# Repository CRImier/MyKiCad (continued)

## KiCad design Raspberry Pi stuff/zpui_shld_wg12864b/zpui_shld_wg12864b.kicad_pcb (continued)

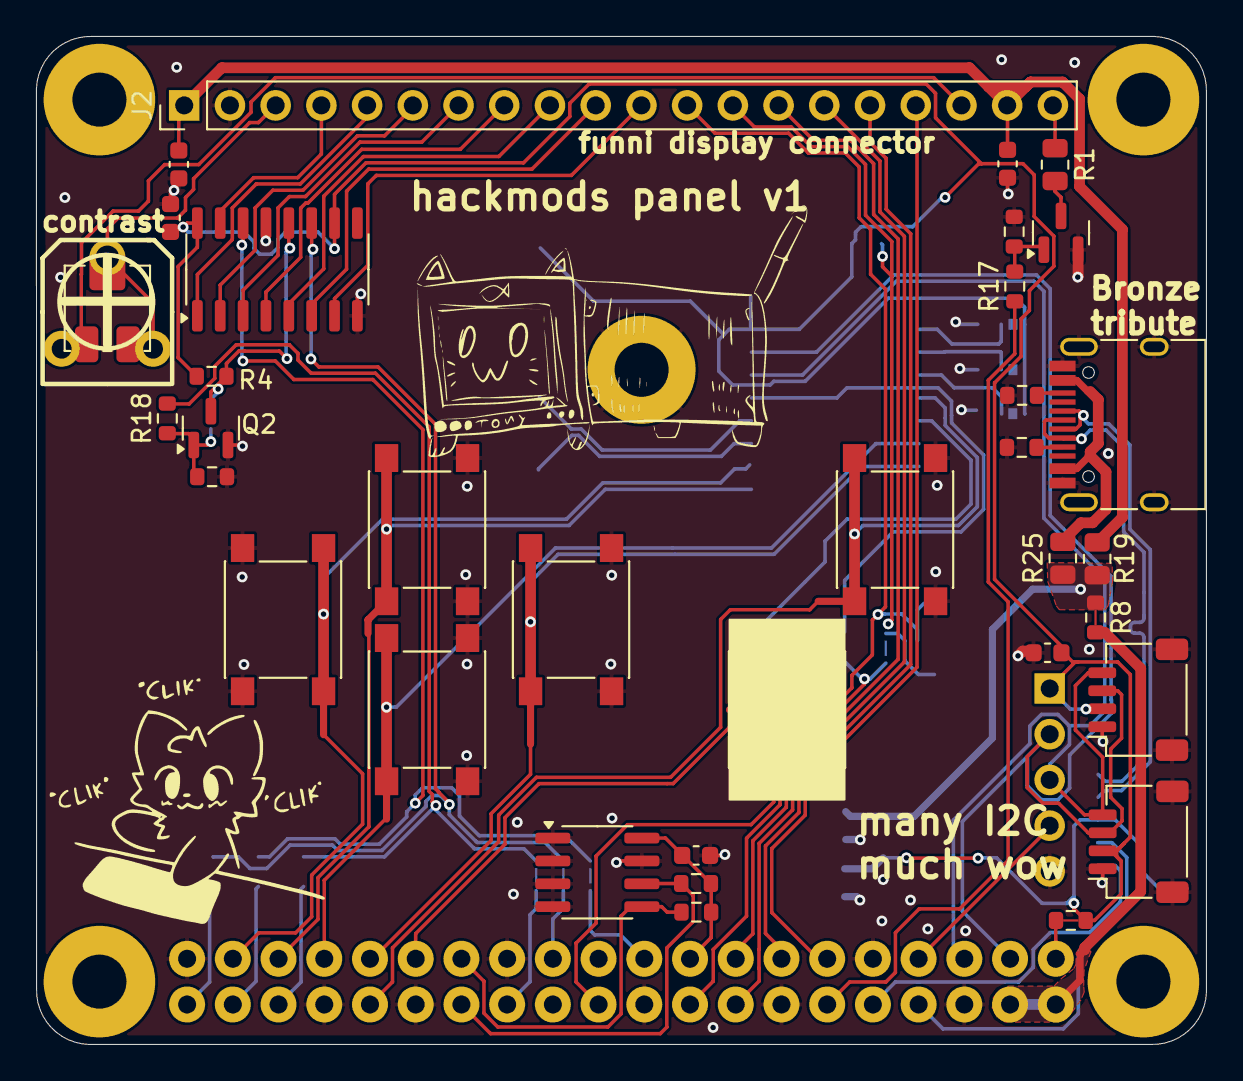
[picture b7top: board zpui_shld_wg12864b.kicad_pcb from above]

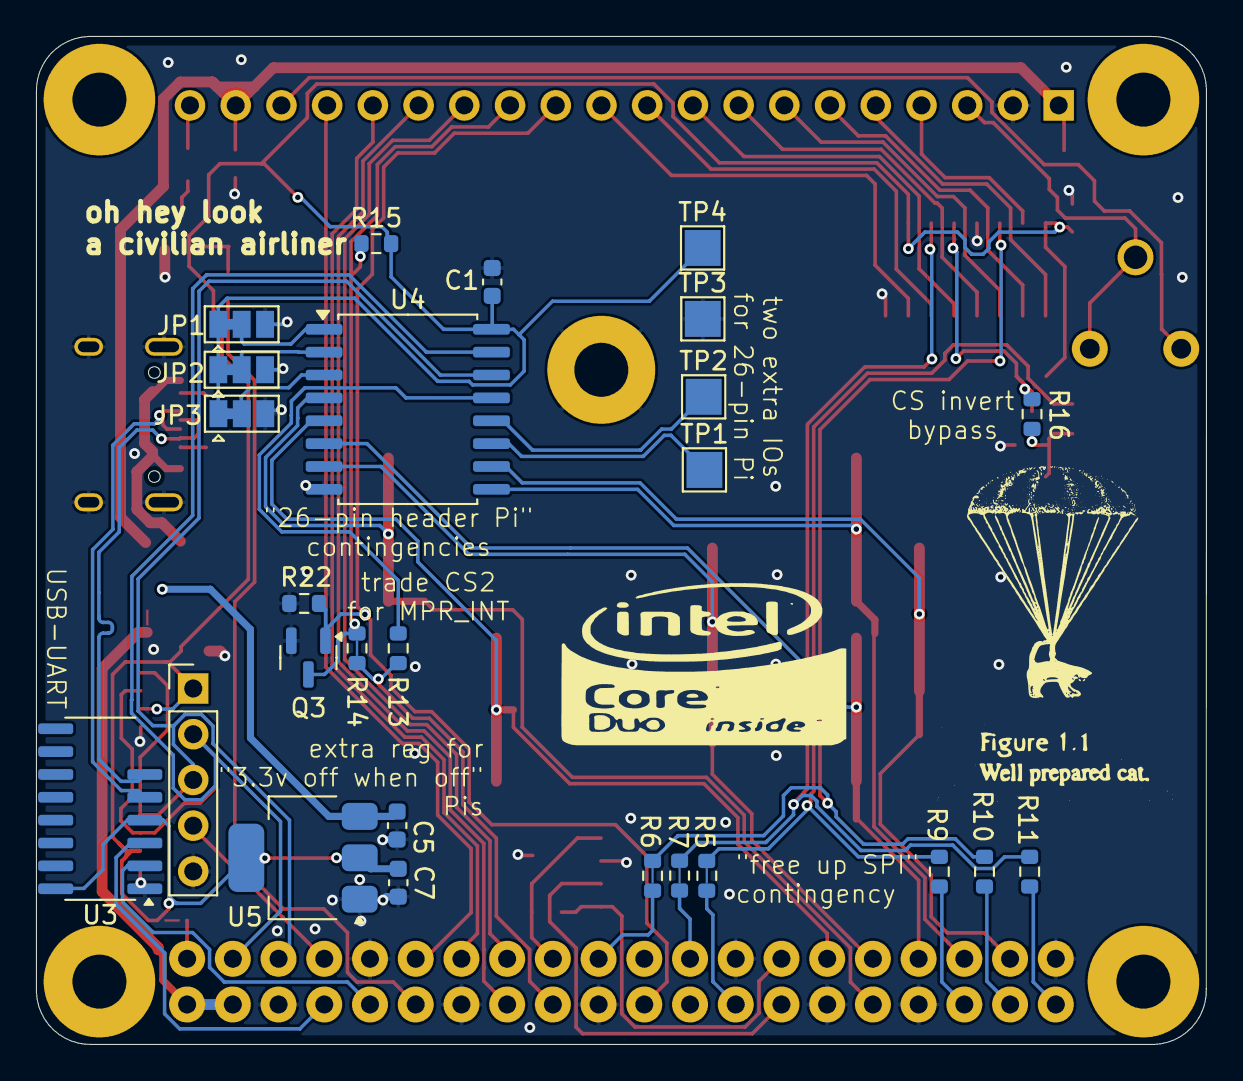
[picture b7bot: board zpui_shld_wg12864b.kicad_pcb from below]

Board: 2 copper layers, 65.0 x 56.0 mm, 63 parts (26 on the bottom side), 63 nets.

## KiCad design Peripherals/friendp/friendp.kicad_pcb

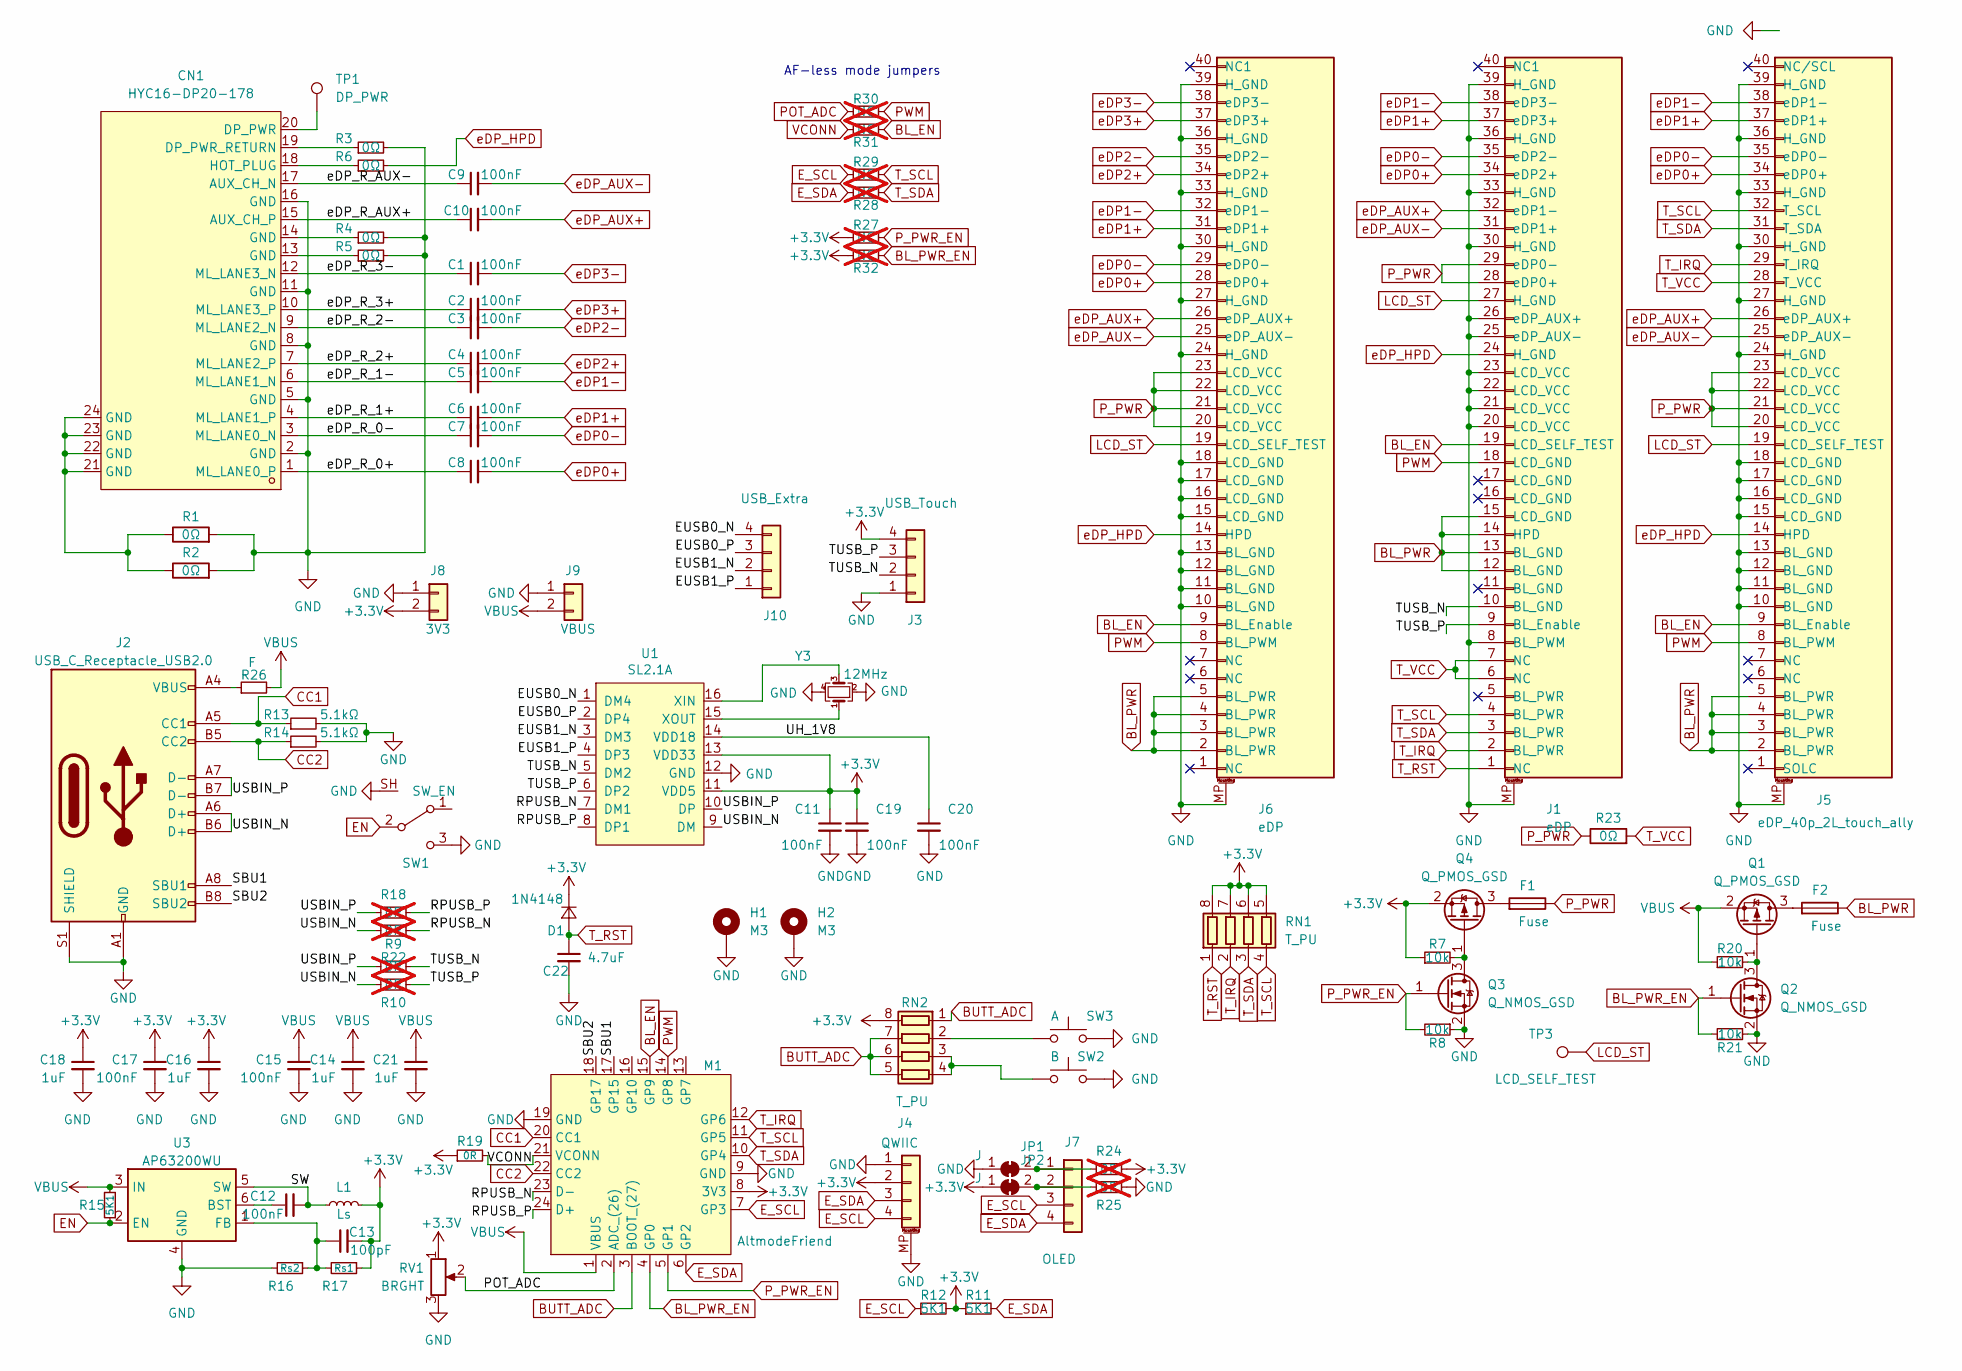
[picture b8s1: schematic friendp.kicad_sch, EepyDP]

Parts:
C1, C2, C3, C4, C5, C6, C7, C8, C9, C10: 100nF; C_0402_1005Metric
C11, C12, C17, C19, C20: 100nF; C_0603_1608Metric
C13: 100pF; C_0603_1608Metric
C14, C16, C18, C21: 1uF; C_0805_2012Metric
C15: 100nF; C_0805_2012Metric
C22: 4.7uF; C_0805_2012Metric
CN1: HYC16-DP20-178; DP-SMD_HYC16-DP20-178; LCSC Part C711350
D1: 1N4148; D_SOD-123F
F1, F2: Fuse; Fuse_0805_2012Metric
H1, H2: M3; MountingHole_3.2mm_M3_Pad
J1, J6: eDP; TE_4-1734839-0_1x40-1MP_P0.5mm_Horizontal
J2: USB_C_Receptacle_USB2.0; USB_C_Receptacle_HRO_TYPE-C-31-M-12
J3: USB_Touch; PinHeader_1x04_P2.54mm_Vertical
J4: QWIIC; JST_SH_SM04B-SRSS-TB_1x04-1MP_P1.00mm_Horizontal
J5: eDP_40p_2L_touch_ally; TE_4-1734839-0_1x40-1MP_P0.5mm_Horizontal
J7: OLED; PinHeader_1x04_P2.54mm_Vertical
J8: 3V3; PinHeader_1x02_P2.54mm_Vertical
J9: VBUS; PinHeader_1x02_P2.54mm_Vertical
J10: USB_Extra; PinHeader_1x04_P2.54mm_Vertical
JP1, JP2: J; R_0603_1608Metric_Jumper
L1: Ls; L_Bourns-SRN4018
M1: AltmodeFriend; altmode_friend
Q1, Q4: Q_PMOS_GSD; SOT-23
Q2, Q3: Q_NMOS_GSD; SOT-23
R1, R2: 0Ω; R_0603_1608Metric
R3, R4, R5, R6, R23: 0Ω; R_0603_1608Metric_Jumper
R7, R8, R20, R21: 10k; R_0603_1608Metric
R9, R10, R18, R22, R24, R25: 0R; R_0603_1608Metric; not fitted
R11, R12, R15: 5K1; R_0603_1608Metric
R13, R14: 5.1kΩ; R_0603_1608Metric
R16: Rs2; R_0603_1608Metric
R17: Rs1; R_0603_1608Metric
R19: 0R; R_0603_1608Metric_Jumper
R26: F; R_0805_2012Metric
R27, R28, R29, R30, R31, R32: NC; R_0603_1608Metric; not fitted
RN1, RN2: T_PU; R_Array_Convex_4x0603
RV1: BRGHT; RES-ADJ-TH_VZ067TL1B202
SW1: SW_EN; SW_SPDT_PCM12_SH
SW2: B; SW_SPST_FSMSM
SW3: A; SW_SPST_FSMSM
TP1: DP_PWR; TestPoint_Pad_1.0x1.0mm
TP3: LCD_SELF_TEST; TestPoint_Pad_1.0x1.0mm
U1: SL2.1A; SO-16_3.9x9.9mm_P1.27mm
U3: AP63200WU; TSOT-23-6
Y3: 12MHz; Crystal_SMD_3225-4Pin_3.2x2.5mm

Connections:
+3.3V: C11.1, C13.2, C16.1, C17.1, C18.1, C19.1, D1.1 (K), J3.4, J4.2, J8.2, JP2.1 (A), L1.2, M1.8 (3V3), Q4.2 (S), R7.1, R11.1, R12.2, R17.1, R19.1, R24.1, R27.1, R32.1, RN1.5 (R4.2), RN1.6 (R3.2), RN1.7 (R2.2), RN1.8 (R1.2), RN2.8 (R1.2), RV1.1, U1.11 (VDD5), U1.13 (VDD33)
/EUSB0_N: J10.4, U1.1 (DM4)
/EUSB0_P: J10.3, U1.2 (DP4)
/EUSB1_N: J10.2, U1.3 (DM3)
/EUSB1_P: J10.1, U1.4 (DP3)
/RPUSB_N: M1.23 (D-), R22.1, U1.7 (DM1)
/RPUSB_P: M1.24 (D+), R18.1, U1.8 (DP1)
/SBU1: J2.A8 (SBU1), M1.17 (GP15)
/SBU2: J2.B8 (SBU2), M1.18 (GP17)
/SW: C12.2, L1.1, U3.5 (SW)
/TUSB_N: J1.10 (BL_GND), J3.2, R9.1, U1.5 (DM2)
/TUSB_P: J1.9 (BL_Enable), J3.3, R10.1, U1.6 (DP2)
/UH_1V8: C20.1, U1.14 (VDD18)
/USBIN_N: J2.A6 (D+), J2.B6 (D+), R10.2, R22.2, U1.9 (DM)
/USBIN_P: J2.A7 (D-), J2.B7 (D-), R9.2, R18.2, U1.10 (DP)
/eDP_R_0+: C8.1, CN1.1 (ML_LANE0_P)
/eDP_R_0-: C7.1, CN1.3 (ML_LANE0_N)
/eDP_R_1+: C6.1, CN1.4 (ML_LANE1_P)
/eDP_R_1-: C5.1, CN1.6 (ML_LANE1_N)
/eDP_R_2+: C4.1, CN1.7 (ML_LANE2_P)
/eDP_R_2-: C3.1, CN1.9 (ML_LANE2_N)
/eDP_R_3+: C2.1, CN1.10 (ML_LANE3_P)
/eDP_R_3-: C1.1, CN1.12 (ML_LANE3_N)
/eDP_R_AUX+: C10.1, CN1.15 (AUX_CH_P)
/eDP_R_AUX-: C9.1, CN1.17 (AUX_CH_N)
BL_EN: J1.19 (LCD_SELF_TEST), J5.9 (BL_Enable), J6.9 (BL_Enable), M1.15 (GP9), R31.2
BL_PWR: F2.1, J1.12 (BL_GND), J1.13 (BL_GND), J1.14 (HPD), J1.15 (LCD_GND), J5.2 (BL_PWR), J5.3 (BL_PWR), J5.4 (BL_PWR), J5.5 (BL_PWR), J6.2 (BL_PWR), J6.3 (BL_PWR), J6.4 (BL_PWR), J6.5 (BL_PWR)
BL_PWR_EN: M1.4 (GP0), Q2.1 (G), R21.2, R32.2
BUTT_ADC: M1.3 (BOOT_(27)), RN2.1 (R1.1), RN2.5 (R4.2), RN2.6 (R3.2), RN2.7 (R2.2)
CC1: J2.A5 (CC1), M1.20 (CC1), R13.1
CC2: J2.B5 (CC2), M1.22 (CC2), R14.1
EN: R15.1, SW1.2 (B), U3.2 (EN)
E_SCL: J4.4, J7.3, M1.7 (GP3), R12.1, R29.1
E_SDA: J4.3, J7.4, M1.6 (GP2), R11.2, R28.1
GND: C11.2, C14.2, C15.2, C16.2, C17.2, C18.2, C19.2, C20.2, C21.2, C22.2, CN1.2 (GND), CN1.5 (GND), CN1.8 (GND), CN1.11 (GND), CN1.16 (GND), H1.1, H2.1, J1.8 (BL_PWM), J1.20 (LCD_VCC), J1.21 (LCD_VCC), J1.22 (LCD_VCC), J1.23 (LCD_VCC), J1.25 (eDP_AUX-), J1.26 (eDP_AUX+), J1.30 (H_GND), J1.33 (H_GND), J1.36 (H_GND), J1.39 (H_GND), J1.MP, J2.A1 (GND), J2.A12 (GND), J2.B1 (GND), J2.B12 (GND), J2.S1 (SHIELD), J3.1, J4.1, J4.MP (MountPin), J5.10 (BL_GND), J5.11 (BL_GND), J5.12 (BL_GND), J5.13 (BL_GND), J5.15 (LCD_GND), J5.16 (LCD_GND), J5.17 (LCD_GND), J5.18 (LCD_GND), J5.24 (H_GND), J5.27 (H_GND), J5.30 (H_GND), J5.33 (H_GND), J5.36 (H_GND), J5.39 (H_GND), J5.MP, J6.10 (BL_GND), J6.11 (BL_GND), J6.12 (BL_GND), J6.13 (BL_GND), J6.15 (LCD_GND), J6.16 (LCD_GND), J6.17 (LCD_GND), J6.18 (LCD_GND), J6.24 (H_GND), J6.27 (H_GND), J6.30 (H_GND), J6.33 (H_GND), J6.36 (H_GND), J6.39 (H_GND), J6.MP, J8.1, J9.1, JP1.1 (A), M1.9 (GND), M1.19 (GND), Q2.2 (S), Q3.2 (S), R1.2, R2.2, R3.2, R4.2, R5.2, R8.1, R13.2, R14.2, R16.2, R21.1, R25.1, RV1.3, SW1.3 (C), SW1.SH, SW2.1, SW3.1, U1.12 (GND), U3.4 (GND), Y3.2, Y3.4
LCD_ST: J1.27 (H_GND), J5.19 (LCD_SELF_TEST), J6.19 (LCD_SELF_TEST), TP3.1
unnamed: CN1.20 (DP_PWR), TP1.1
unnamed: CN1.19 (DP_PWR_RETURN), R3.1
unnamed: CN1.13 (GND), R5.1
unnamed: CN1.14 (GND), R4.1
unnamed: CN1.21 (GND), CN1.22 (GND), CN1.23 (GND), CN1.24 (GND), R1.1, R2.1
unnamed: CN1.18 (HOT_PLUG), R6.1
unnamed: J2.A4 (VBUS), J2.A9 (VBUS), J2.B4 (VBUS), J2.B9 (VBUS), R26.1
unnamed: J7.1, JP1.2 (B), R24.2
unnamed: J7.2, JP2.2 (B), R25.2
unnamed: F2.2, Q1.3 (D)
unnamed: Q1.1 (G), Q2.3 (D), R20.2
unnamed: Q3.3 (D), Q4.1 (G), R7.2
unnamed: F1.2, Q4.3 (D)
unnamed: RN2.2 (R2.1), SW3.2
unnamed: RN2.3 (R3.1), RN2.4 (R4.1), SW2.2
unnamed: U1.16 (XIN), Y3.3
unnamed: U1.15 (XOUT), Y3.1
unnamed: C12.1, U3.6 (BST)
unnamed: C13.1, R16.1, R17.2, U3.1 (FB)
POT_ADC: M1.2 (ADC_(26)), R30.1, RV1.2
PWM: J1.18 (LCD_GND), J5.8 (BL_PWM), J6.8 (BL_PWM), M1.14 (GP8), R30.2
P_PWR: F1.1, J1.28 (eDP0+), J1.29 (eDP0-), J5.20 (LCD_VCC), J5.21 (LCD_VCC), J5.22 (LCD_VCC), J5.23 (LCD_VCC), J6.20 (LCD_VCC), J6.21 (LCD_VCC), J6.22 (LCD_VCC), J6.23 (LCD_VCC), R23.1
P_PWR_EN: M1.5 (GP1), Q3.1 (G), R8.2, R27.2
T_IRQ: J1.2 (BL_PWR), J5.29 (T_IRQ), M1.12 (GP6), RN1.2 (R2.1)
T_RST: C22.1, D1.2 (A), J1.1 (NC), RN1.1 (R1.1)
T_SCL: J1.4 (BL_PWR), J5.32 (T_SCL), M1.11 (GP5), R29.2, RN1.4 (R4.1)
T_SDA: J1.3 (BL_PWR), J5.31 (T_SDA), M1.10 (GP4), R28.2, RN1.3 (R3.1)
T_VCC: J1.6 (NC), J1.7 (NC), J5.28 (T_VCC), R23.2
VBUS: C14.1, C15.1, C21.1, J9.2, M1.1 (VBUS), Q1.2 (S), R15.2, R20.1, R26.2, U3.3 (IN)
VCONN: M1.21 (VCONN), R19.2, R31.1
eDP0+: C8.2, J1.34 (eDP2+), J5.34 (eDP0+), J6.28 (eDP0+)
eDP0-: C7.2, J1.35 (eDP2-), J5.35 (eDP0-), J6.29 (eDP0-)
eDP1+: C6.2, J1.37 (eDP3+), J5.37 (eDP1+), J6.31 (eDP1+)
eDP1-: C5.2, J1.38 (eDP3-), J5.38 (eDP1-), J6.32 (eDP1-)
eDP2+: C4.2, J6.34 (eDP2+)
eDP2-: C3.2, J6.35 (eDP2-)
eDP3+: C2.2, J6.37 (eDP3+)
eDP3-: C1.2, J6.38 (eDP3-)
eDP_AUX+: C10.2, J1.32 (eDP1-), J5.26 (eDP_AUX+), J6.26 (eDP_AUX+)
eDP_AUX-: C9.2, J1.31 (eDP1+), J5.25 (eDP_AUX-), J6.25 (eDP_AUX-)
eDP_HPD: J1.24 (H_GND), J5.14 (HPD), J6.14 (HPD), R6.2

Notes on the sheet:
AF-less mode jumpers

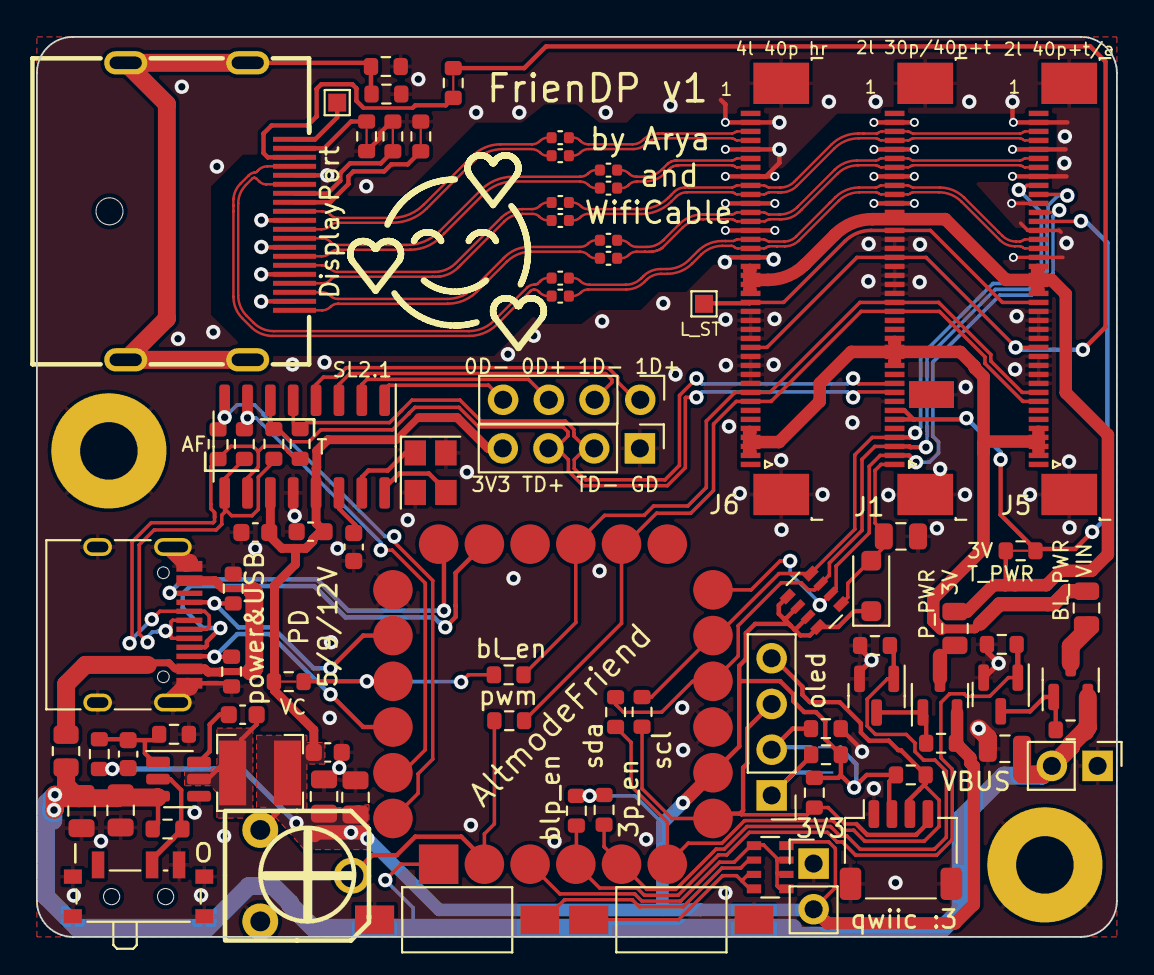
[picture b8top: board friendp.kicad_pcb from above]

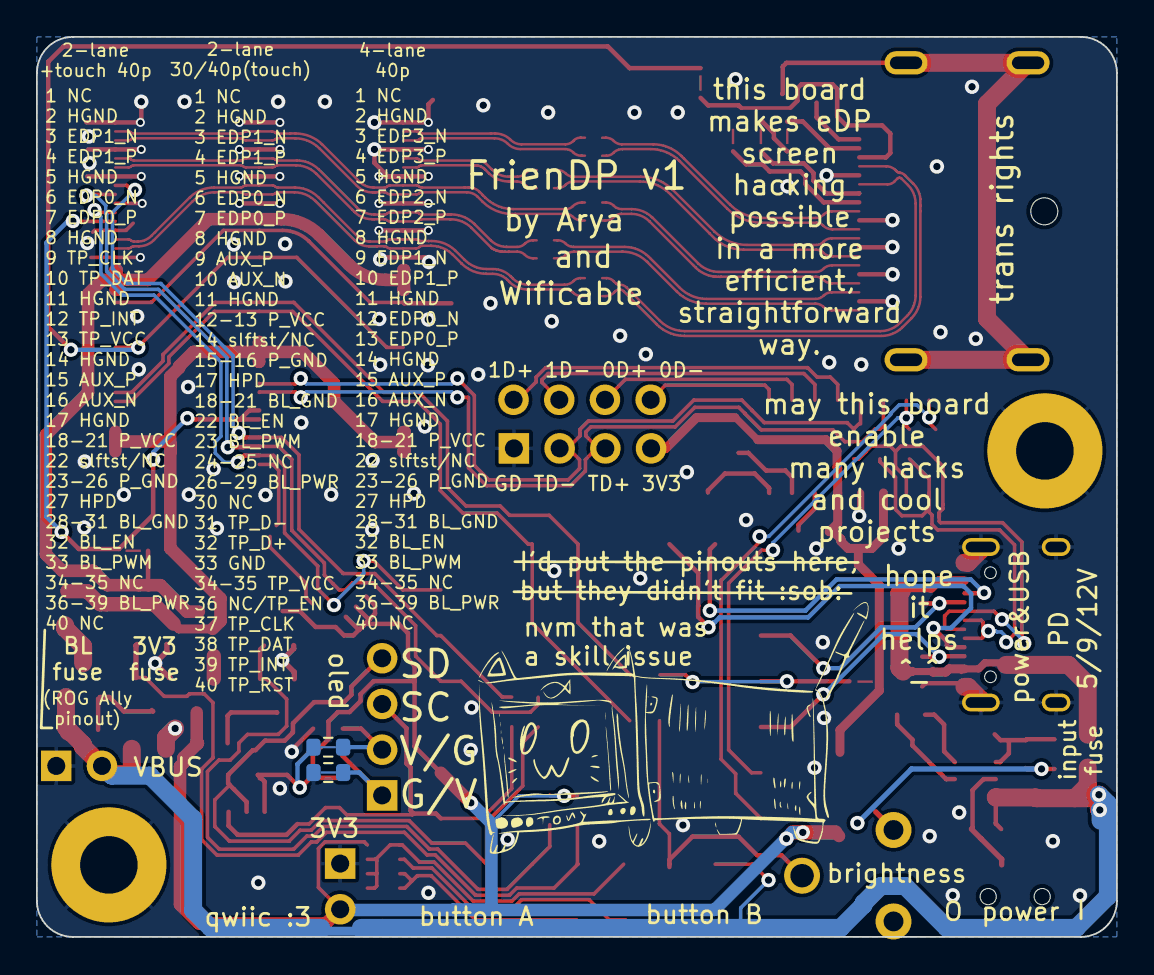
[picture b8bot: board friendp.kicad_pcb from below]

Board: 4 copper layers, 60.0 x 50.0 mm, 89 parts (2 on the bottom side), 77 nets.

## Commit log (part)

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2019-07-22 Feeling lucky, might push -f later
2019-10-12 Adding fp-info-cache to .gitignore
2019-10-12 Adding "rescue" files to gitignore
2019-10-12 Adding SaferSpace files
2019-11-12 Adding SY6280 breakout - v1 finished
2019-11-12 Adding the 74HC125-1G breakout (need to check footprint)
2019-11-12 Adding the 74HC245 DIP breakout - v1, should work
2019-11-15 595 SMD breakout changes (forgot what exactly)
2019-11-15 PCF8574 breakout WIP
2019-11-15 SY6280 breakout changes (forgot what exactly)
2019-11-15 74HC245 breakout changes (forgot what exactly)
2019-11-15 Pi PWM breakout changes (forgot what exactly)
2019-11-15 PCF8574 breakout - directory was not created correctly, moving
2019-11-15 PCF8574 breakout: did not close KiCad before commit, fixing
2019-11-18 Blank files for Ericsson PKF4000 breakout
2019-11-18 Adding PKF4000 datasheet
2019-11-19 Generating gerbers, adding some silk to the PCF8574 board
2019-11-19 Adding the 4x NPN breakout PCB
2019-11-19 Adding the S29ALxxxD breakout
2020-03-04 Adding power lane 90 degree arc PCBs for 2 and 3 lanes, 2 and 4 cm radius
2020-03-04 Removing fp-info-cache file
2020-03-04 Adding SIM net labels to mPCI-E breakout - SIM slot not fixed yet
2020-03-04 Improving MakeRiga keychain PCBs
2020-03-04 Minor PCF8574 breakout changes
2020-03-04 Adding MicroUSB breakouts - with and without a 3.3V regulator spot
2020-03-04 Adding files for a small power bus with a cap
2020-03-04 Parallel EEPROM reader files - not tested or anything, do not rely on it
2020-03-04 Gitignore-ing a bunch of stuff
2020-03-04 Adding self-playing piano solenoid controller PCB - P transistor footprint has wrong pinout and one of the 2-pin power connector footprints has reverse polarity, needs to be fixed.
2020-03-09 Adding a README for the Keyboard Whiz
2020-03-28 Adding Lenovo Flex 2-14 reverse-engineering top assembly FPC reverse-engineering effort
2020-08-26 Fixing confusion with Lenovo Flex 2 14 reverse-engineering files
2020-10-15 Adding JST-SH 4-pin and 6-pin breakouts
2020-10-15 Adding MAX14689 breakout files
2020-10-15 Adding a README to the microusb_breakout_with_reg board, with a small bug disclaimer.
2020-10-15 Fixing the microusb_breakout_with_reg board bug and removing the README disclaimer
2020-10-15 Adding the laptop_smartcard_socket_fpc_breakout board
2020-10-15 Adding *.sch-bak files to gitignore
2020-10-15 Changing the 48V relay breakout board so that all the SMD components are mounted on the bottom side => easier to assemble
2020-11-06 Adding the Raspberry Pi 400 GPIO adapter files - v1
2020-11-08 Adding README, pictures and proper 3d models to the Pi 400 GPIO adapter board
2021-01-05 Pi 400 GPIO breakout v2. Adding this in part because I'll try to re-route it now and might fail at that, so will need to fall back to the previous version.
    Force pushed later on - forgot to regenerate zones.
2021-01-05 Updated version of the fan_pwm_disconnecter board, this is what I'll be ordering
2021-01-15 Adding x2 panel files for mPCIe breakout board
2021-01-15 Adding TTP229BSF breakout board files with README
2021-01-15 Adding fan_pwm_disconnecter panel files
2021-01-15 Gitignore-ing panel gerber folders
2021-01-15 Adding a template line for "this repo also contains panel files"
2021-09-26 Updating and renaming a 48V relay breakout PCB, sch is broken and no idea how to fix it, really - maybe eventually. Also adding a 2x9 panel that fits inside JLCPCB 10x10 dimensions, though will take 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
2021-09-26 Adding a README and changing the on-PCB text to say "v2" because that's what it is. Need to also update the panel text sometime soon.
2021-09-26 Video I2C helper v1 added
2021-10-01 Added an 0R resistor in series with VCC on the simple NPN driver
2021-10-04 Adding the ATTIny universal fan controller board - unchecked for now, will be going over it later
2021-10-04 gitignore-ing the .pdf and .svg files again, also adding panel gerber folders to gitignore
2021-10-05 Adding Display Debuggaloo board v1
2021-10-05 Adding yet another MakeRiga keychain
2021-10-12 Adding the Pinecil 24V enjoyer board
2021-10-13 Adding the 0.69 display breakout
2021-10-15 Changed the HDMI plug in the Video I2C helper to correct pin numbering, rerouted traces to match, added shield connection to the SPDT switch symbol and pinout
2021-10-15 This is GPLv3, always has been
2021-10-15 Adding a "recommended thickness" line, adding it to READMEs where it fits
2021-10-15 Adding the uSD FPC breakout board
2021-10-17 Adding the K1-1210UN-01 switch breakout, with symbol and footprint
2021-10-18 Moving the MicroUSB socket to the top layer so that the board is easier to assemble, rearranging silkscreen a bit
2021-10-20 Adding the small MAX3232 breakout
2021-10-20 Adding a B+M to M-key 2230-2242 adapter
2021-10-20 Removing a bit of unneeded text
2021-10-27 Adding the reversed mPCIe to NVMe adapter. A non-reversed version coming soon!
2021-10-27 Adding more documentation to the NVMe BM to M card README
2021-11-03 Adding the mPCIe-NVMe board (non-reversed)
2021-11-03 Rerouted diffpairs to NVMe BM to M adapter, made the adapter longer, added holes so that part of the adapter can be snipped off for length decrease
2021-11-05 Adding the USB-B-to-MicroUSB board files, from https://gitlab.com/salfter/arduino-micro-usb-mod, then modified by me
2021-11-05 Adding the USB-A to Type-C converter board
2021-11-05 Adding the Neopixel to RS485 board
2021-11-05 Adding the single-sided version of the Neopixel to RS485 board
2021-11-07 Adding an ADJ resistor to the 1117-15 on the backside, rerouting diffpairs to decrease impedance a little bit
2021-11-07 Gerber export setting fixes - mostly changing "(excludeedgelayer false)" to "true)"
2021-11-09 Enabling more layers for export in the Tizen uSD breakout
2021-11-09 Fixing a README typo
2021-11-10 Adding a Type-C receptacle with holes-for-slots - just in case it's ever needed ig?
2021-11-10 Adding an M.2 AE to M-key adapter
2021-11-16 Adding a README to the repo itself, also adding the make_gml.py script.
2021-11-16 Fixing the silkscreen resistor numbers on the mPCIe-NVMe board
2021-11-16 Reloading the simple FET power path project files
2021-11-16 Re-exporting fiducial PCBs - they'll need a README eventually too, ig
2021-11-16 Changing the USB power switcher dimensions to be more reasonable, adding a README
2021-11-16 Staggering the Pi I2C shifter pins, adding a reference to that to the README
2021-11-18 Adding a power LED to the video I2C breakout, rerouting traces a bit to accomodate for that
2021-11-20 Adding the NVMe to dual SSD (PCI-E native + SATA hack) adapter
2021-11-20 Adding the M.2 to dual SSD (SATA native + PCI-E hack) adapter
2021-11-21 Small fan controller PCB trace changes
2021-11-22 Moving aux origin axis a bit on display debuggaloo
2021-11-25 Adding the Type-C interposer board
2021-11-25 Adding a "PCB & README count" script
2021-12-19 Fixing small issue on the video I2C board, bumping it to v2
2021-12-23 ProtoESP schematic v2. Will be moved into the ESP32 directory next.
2021-12-24 ProtoESP schematic day 3
2021-12-27 ProtoESP work day 5, oh wait, actually, 6!
2021-12-27 Day 6 continuation - mousebites done
2021-12-29 ProtoESP work day 8, part A
2022-01-08 Adding the SaferSpace ESP12 entry panel controller PCB - v1
2022-01-15 Latest updates - consider this v1.1 ;-P
2022-01-15 Release script!
2022-05-02 Excluding STEP file from source release, for space saving purposes
2022-05-08 Adding start of work on the Framework input connector breakout
2022-05-08 Warning added
2022-05-08 Silkscreen for input-side connector was confusing - fixed
2022-05-11 Adding first rev of Framework input shim
2022-05-15 framework_input_controller: adding first rev
2022-05-15 framework_input_controller: README addition about two extra USB ports
2022-05-15 framework_input_brkt_smol: added warning about v1 being very broken
2022-05-16 framework_input_controller: adding fiducials, rerouting a few tracks, tweaking silk, adding silk clarifications and warnings
2022-05-17 framework_input_brkt_smol: v2, fixed the critical pinout error and rerouted the board; added the caps lock LED connections
2022-08-31 Adding more useful lines to my template file
2022-08-31 Adding some more entries to .gitignore
2022-09-20 keyboardwhiz: v3, a RP2040+expanders version that also allows for some chip shortage failsafes
2022-09-20 18650_pcb: adding v2 (way more advanced) and adding README for it
2022-09-20 video_i2c_breakout: v2, functional changes
2022-09-20 mpcie_breakout: v3 files + panel files
2022-10-12 mpcie_nvme: unknown PCB changes, some traces it'd seem
2022-10-12 framework_input_controller: moved to KiCad 6
2022-10-12 nvme_to_dual_ssd: Forgotten README changes, adding
2022-10-19 pi_spiflash_shim: moving text a bit, removing a prl file from git
2022-10-19 TEMPLATE.md: updating stubs, turning notes into bullet points for readability
2022-10-19 Adding kicad6 move check script, updating the stats script and updating readme for these
2022-10-19 nvme_bm_to_m: v2, removed caps, changed shape, isolated one ambiguous pin, updated README
2022-11-11 protoesp: added battery onboard fuse, updated to KiCad6, small script tweaks, changed name
2022-11-11 10p_fpc_breakout: adding v1
2022-11-12 .gitignore: panel and Nano editor files
2022-11-13 usbc_hs_female_breakout: v1
2022-11-14 framework_mobo_lefthalf: WIP
2022-11-14 altmode_friend: v1
2022-12-14 framework_mobo_lefthalf: WIP some more, separated stuff into topleft and bottomleft; added display footprint from imnotjames; looking out for any routing hiccups in highspeed stuff. is gonna be 6 lay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
2023-01-11 usbc_power_breakout_af: v1, adding Altmode Friend power devboard
2023-01-11 more gitignore
2023-05-04 usbc_debug_finder: v1
2023-05-04 .gitignore: CSV BOM files
2023-07-18 satappy: v1
2023-07-18 mpcie_nvme_reversed: updating some of the files; updated to KiCad 7; updated README
2023-07-18 simple_keeb_reuser: v1
2023-08-03 hapticbelt_driver: v1
2023-08-05 fan_controller: bringing to kicad7
2023-08-12 framework_ic_keeb_adapter: v1
2023-08-12 pam2306_breakout: v1
2023-08-12 usbc_debug_finder: v1 (new, actual to-be-ordered)
2023-11-20 Adding Sony Vaio RE board - in-progress
2024-02-14 hapticbelt_driver: actually manufactured v1 version, with seriously improved silk
2024-02-14 TEMPLATE.md: default kicad version updated to 7, just in time for kicad 8
2024-02-14 .gitignore: lockfile ignore
2024-02-14 18650_pcb: WIP v3, added USB-C socket for charging, need to fix silk
2024-02-14 usbc_debug_finder: slight README tweak
2024-02-14 .gitignore: further production file improvements
2024-02-14 display_debuggaloo: updating to kicad 7
2024-02-15 nep_hackerboard: v1 (WIP)
2024-02-19 Libs: rtl2832 symbol (untested)
2024-03-11 18650_pcb: proper v3, added usb-c socket usb data breakout, mounting holes on corners, improved silk including LED warnings, rerouted LEDs for short-circuit protection with 18650 hoplder pads
2024-03-11 framework_input_controller: production-ready panel
2024-03-11 framework_input_controller: iirc latest version as produced, changes not known
2024-03-22 Add gitbug workflow for rendering pcb images
2024-03-24 remove render.sh and render images next to pcb file
2024-03-24 replace GITHUB_WORKSPACE with github.workspace
2024-03-24 add example for images in README.md
2024-05-16 friendp: initial commit; WIP but almost finished
2024-05-21 sony_vaio_p_re: WIP
2024-05-24 sony_vaio_p_re: working away
2024-05-25 sony_vaio_p_re: more work; power management PoC done
2024-05-28 sony_vaio_p_re: some more additions
2024-05-30 sony_vaio_p_re: hacking continues
2024-06-02 sony_vaio_p_re: Some More Hacks
2024-06-05 sony_vaio_p_re: moar good additions :3
2024-06-06 sony_vaio_p_re: silky smooth progress
2024-06-12 sony_vaio_p_re: surely certainly the last changes possible
2024-06-15 sony_vaio_p_re: prettified schematic, fixed usb mux default state, also this happens to be a version that jlcpcb would like to assemble
2024-06-24 zpui_shld_wg12864b: v0
2024-06-24 zpui_shld_wg12864b: v0.0
2024-11-03 fluff: readme slightly updated
2024-11-18 zpn_devboard: wip
2025-02-01 zpui_businesscard: v1, as manufactured
2025-03-20 zpn_devboard: v0; needs review before ordering
2025-03-20 zpn_devboard: 4G modem submodule added
2026-01-19 ptn3222_breakout: v1
